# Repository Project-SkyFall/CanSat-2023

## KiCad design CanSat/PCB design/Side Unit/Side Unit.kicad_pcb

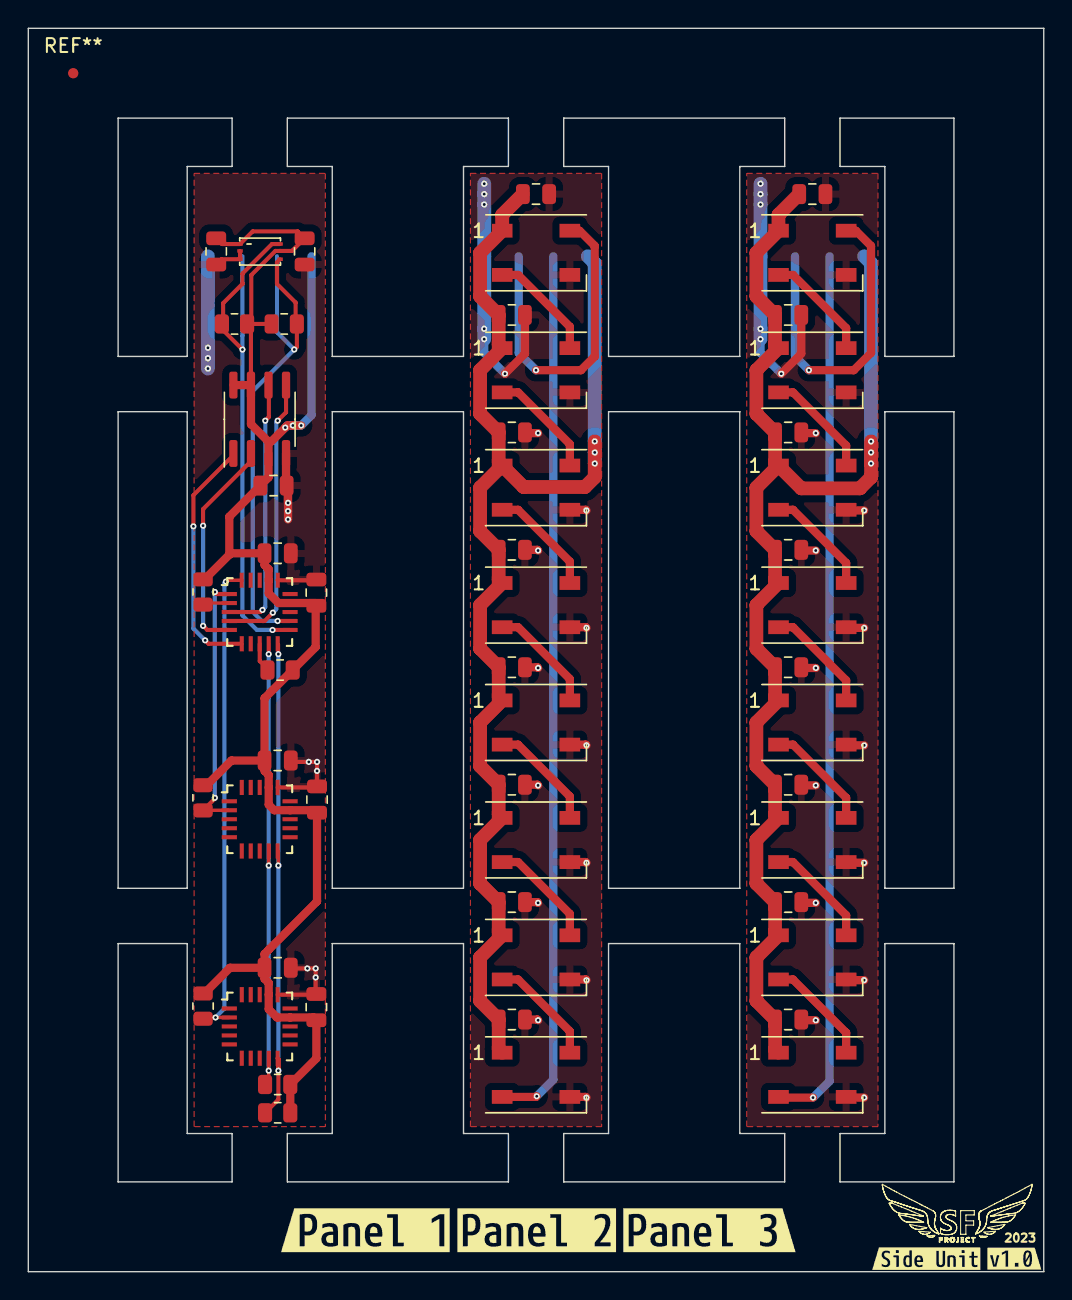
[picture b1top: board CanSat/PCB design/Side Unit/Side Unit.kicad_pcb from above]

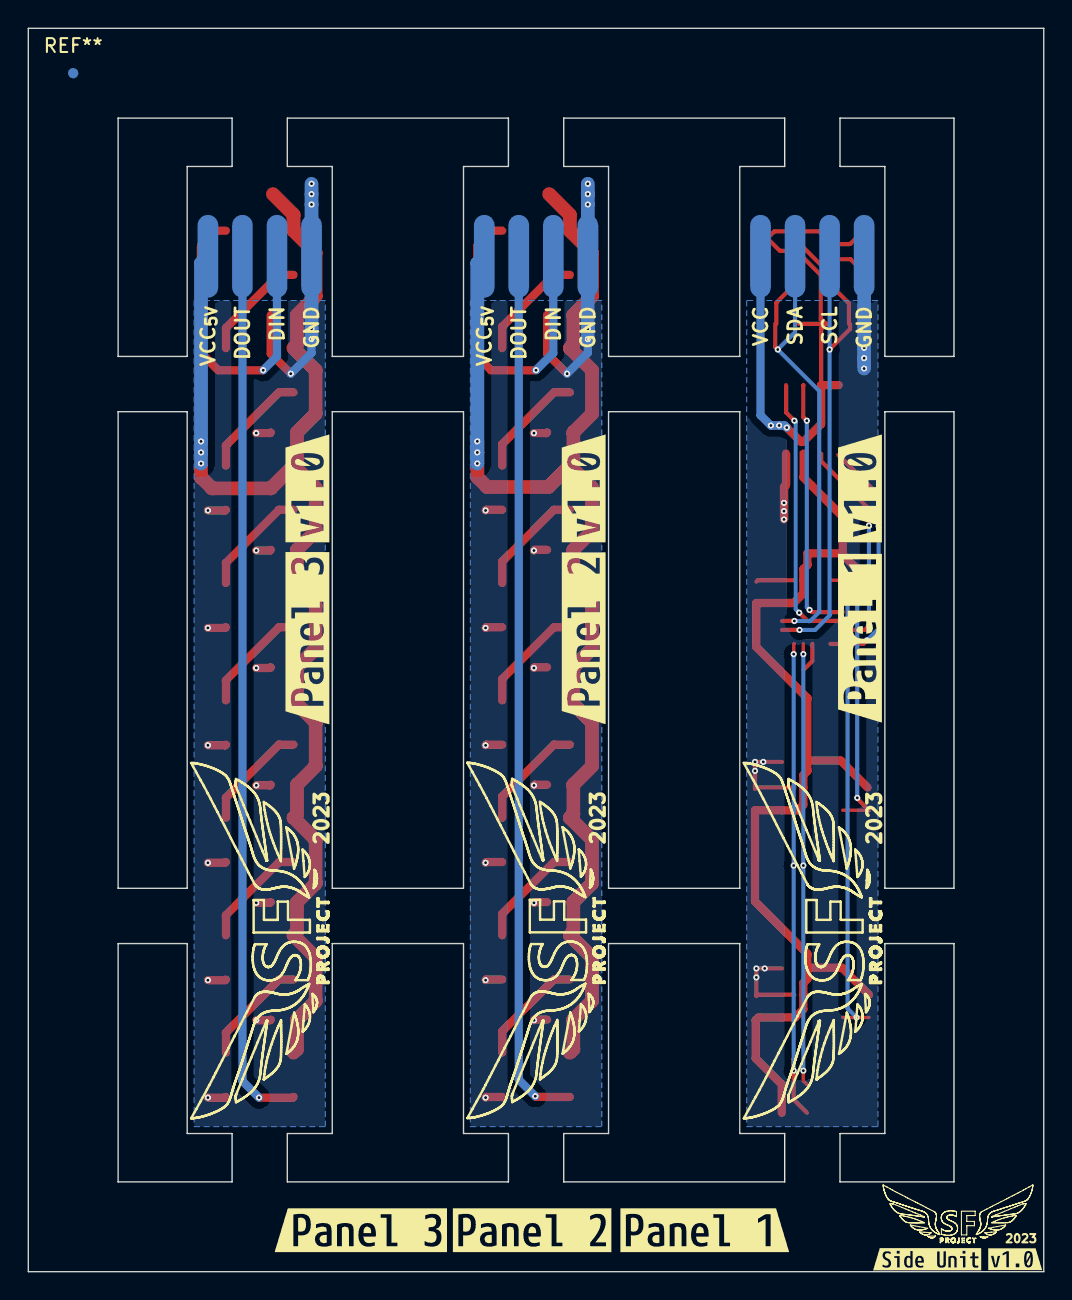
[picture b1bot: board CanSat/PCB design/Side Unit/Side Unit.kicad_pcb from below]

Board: 2 copper layers, 73.5 x 90.0 mm, 73 parts (14 on the bottom side), 36 nets.

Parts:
C301, C303, C305, C401, C402, C501, C502, C503, C504, C505, C506, C507, C508, C601, C602, C603, C604, C605, C606, C607, C608: 0.1uF; C_0805_2012Metric
C302, C304, C306, C307: 1uF; C_0805_2012Metric
D501, D502, D503, D504, D505, D506, D507, D508, D601, D602, D603, D604, D605, D606, D607, D608: WS2812B; LED_WS2812B_PLCC4_5.0x5.0mm_P3.2mm
J101, J102, J103: Land patern; Land-pattern
R201, R202, R301, R302, R303, R304, R305, R306: 10k; R_0805_2012Metric
U301: AS72651; AMS_LGA-20_4.7x4.5mm_P0.65mm
U302: AS72652; AMS_LGA-20_4.7x4.5mm_P0.65mm
U303: AS72653; AMS_LGA-20_4.7x4.5mm_P0.65mm
U304: AT25SF041B-SSHD-B; SOIC-8_3.9x4.9mm_P1.27mm
U401: BH1730; WSOF6
kibuzzard-63C42A2A: G***; kibuzzard-63C42A2A
kibuzzard-63C42A5F, kibuzzard-63C42A5F#2, kibuzzard-63C42A5F#3: G***; kibuzzard-63C42A5F
kibuzzard-63C42B4A: G***; kibuzzard-63C42B4A
kibuzzard-63C42B39: G***; kibuzzard-63C42B39
kibuzzard-63C86FC3: G***; kibuzzard-63C86FC3
kibuzzard-63C86FCE: G***; kibuzzard-63C86FCE
kibuzzard-63C685CC, kibuzzard-63C685CC#2: G***; kibuzzard-63C685CC
kibuzzard-63C685D8, kibuzzard-63C685D8#2: G***; kibuzzard-63C685D8
kibuzzard-63C6862F: G***; kibuzzard-63C6862F
kibuzzard-63C68642, kibuzzard-63C68642#2: G***; kibuzzard-63C68642
kibuzzard-63C68658: G***; kibuzzard-63C68658

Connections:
/Panel 1/GND: C301.2, C302.2, C303.2, C304.2, C305.2, C306.2, C307.2, C401.1, C402.2, J101.1, U301.16 (GND), U302.16 (GND), U303.16 (GND), U304.4 (GND), U401.2 (INT), U401.3 (GND)
/Panel 1/SCL: J101.2, R202.2, U301.11 (RX/SCL_S), U401.6 (SCL)
/Panel 1/SDA: J101.3, R201.2, U301.12 (TX/SDA_S), U401.4 (SDA)
/Panel 1/Spectroscope Unit/MISO: U301.5 (MISO), U304.2 (SO_(IO1_))
/Panel 1/Spectroscope Unit/MOSI: U301.4 (MOSI), U304.5 (SI_(IO0_))
/Panel 1/Spectroscope Unit/SCK: U301.3 (SCK), U304.6 (SCK)
/Panel 1/Spectroscope Unit/SCL_S: R304.2, U301.9 (SCL_M), U302.9 (SCL_S), U303.9 (SCL_S)
/Panel 1/Spectroscope Unit/SDA_S: R303.2, U301.10 (SDA_M), U302.10 (SDA_S), U303.10 (SDA_S)
/Panel 1/Spectroscope Unit/~CS: U301.6 (~CS), U304.1 (~CS)
/Panel 1/Spectroscope Unit/~RES: R306.2, U301.2 (~RES)
/Panel 1/Spectroscope Unit/~SLV1_RES: R302.2, U301.1 (~SLV1_RES), U302.2 (~RES)
/Panel 1/Spectroscope Unit/~SLV2_RES: R301.2, U301.20 (~SLV2_RES), U303.2 (~RES)
/Panel 1/VCC: C301.1, C302.1, C303.1, C304.1, C305.1, C306.1, C307.1, C401.2, C402.1, J101.4, R201.1, R202.1, R301.1, R302.1, R303.1, R304.1, R305.1, R306.1, U301.14 (VDD2), U301.17 (VDD1), U302.14 (VDD2), U302.17 (VDD1), U303.14 (VDD2), U303.17 (VDD1), U304.3 (~WP_(IO2_)), U304.7 (~HOLD_(IO3_)), U304.8 (VCC), U401.1 (VCC), U401.5 (DVI)
/Panel 2/DIN: D501.4 (DIN), J102.2
/Panel 2/DOUT: D508.2 (DOUT), J102.3
/Panel 2/GND: C501.1, C502.1, C503.1, C504.1, C505.1, C506.1, C507.1, C508.1, D501.3 (VSS), D502.3 (VSS), D503.3 (VSS), D504.3 (VSS), D505.3 (VSS), D506.3 (VSS), D507.3 (VSS), D508.3 (VSS), J102.1
/Panel 2/VCC_5V: C501.2, C502.2, C503.2, C504.2, C505.2, C506.2, C507.2, C508.2, D501.1 (VDD), D502.1 (VDD), D503.1 (VDD), D504.1 (VDD), D505.1 (VDD), D506.1 (VDD), D507.1 (VDD), D508.1 (VDD), J102.4
/Panel 3/DIN: D601.4 (DIN), J103.2
/Panel 3/DOUT: D608.2 (DOUT), J103.3
/Panel 3/GND: C601.1, C602.1, C603.1, C604.1, C605.1, C606.1, C607.1, C608.1, D601.3 (VSS), D602.3 (VSS), D603.3 (VSS), D604.3 (VSS), D605.3 (VSS), D606.3 (VSS), D607.3 (VSS), D608.3 (VSS), J103.1
/Panel 3/VCC_5V: C601.2, C602.2, C603.2, C604.2, C605.2, C606.2, C607.2, C608.2, D601.1 (VDD), D602.1 (VDD), D603.1 (VDD), D604.1 (VDD), D605.1 (VDD), D606.1 (VDD), D607.1 (VDD), D608.1 (VDD), J103.4
unnamed: D501.2 (DOUT), D502.4 (DIN)
unnamed: D502.2 (DOUT), D503.4 (DIN)
unnamed: D503.2 (DOUT), D504.4 (DIN)
unnamed: D504.2 (DOUT), D505.4 (DIN)
unnamed: D505.2 (DOUT), D506.4 (DIN)
unnamed: D506.2 (DOUT), D507.4 (DIN)
unnamed: D507.2 (DOUT), D508.4 (DIN)
unnamed: D601.2 (DOUT), D602.4 (DIN)
unnamed: D602.2 (DOUT), D603.4 (DIN)
unnamed: D603.2 (DOUT), D604.4 (DIN)
unnamed: D604.2 (DOUT), D605.4 (DIN)
unnamed: D605.2 (DOUT), D606.4 (DIN)
unnamed: D606.2 (DOUT), D607.4 (DIN)
unnamed: D607.2 (DOUT), D608.4 (DIN)
unnamed: R305.2, U301.8 (I2C_ENB)

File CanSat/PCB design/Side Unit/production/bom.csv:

Designator,Footprint,Quantity,Value,LCSC Part #
"C301, C303, C305, C401, C402, C501, C502, C503, C504, C505, C506, C507, C508, C601, C602, C603, C604, C605, C606, C607, C608",C_0805_2012Metric,21,100nF,
"C302, C304, C306, C307",C_0805_2012Metric,4,1uF,
"D501, D502, D503, D504, D505, D506, D507, D508, D601, D602, D603, D604, D605, D606, D607, D608",LED_WS2812B_PLCC4_5.0x5.0mm_P3.2mm,16,WS2812B,
"R201, R202, R301, R302, R303, R304, R305, R306",R_0805_2012Metric,8,10k,
U301,AMS_LGA-20_4.7x4.5mm_P0.65mm,1,AS72651,
U302,AMS_LGA-20_4.7x4.5mm_P0.65mm,1,AS72652,
U303,AMS_LGA-20_4.7x4.5mm_P0.65mm,1,AS72653,
U304,SOIC-8_3.9x4.9mm_P1.27mm,1,AT25SF041B-SSHD-B,
U401,WSOF6,1,BH1730,

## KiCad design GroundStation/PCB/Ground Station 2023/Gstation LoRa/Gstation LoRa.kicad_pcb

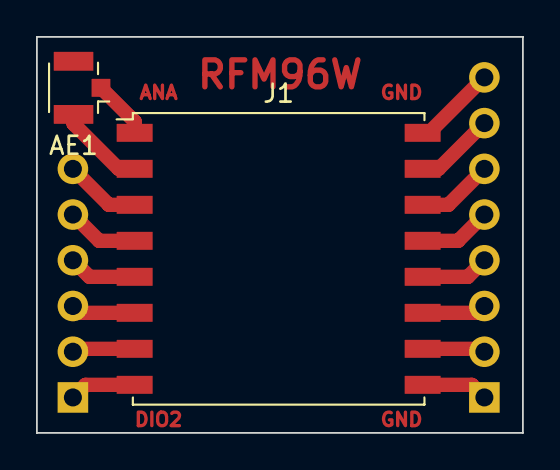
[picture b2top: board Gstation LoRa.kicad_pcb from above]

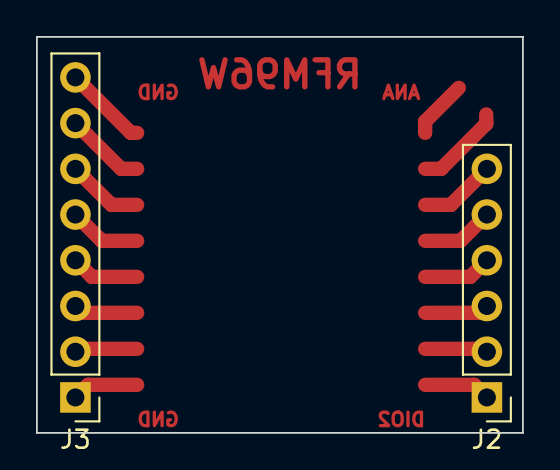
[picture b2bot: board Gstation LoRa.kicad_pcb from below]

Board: 2 copper layers, 27.0 x 22.0 mm, 4 parts (2 on the bottom side), 16 nets.

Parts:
AE1: Antenna_Shield; U.FL_Hirose_U.FL-R-SMT-1_Vertical
J1: Conn_02x08_Counter_Clockwise; HOPERF_RFM9XW_SMD
J2: Conn_01x06_Male; PinHeader_1x06_P2.54mm_Vertical
J3: Conn_01x08_Male; PinHeader_1x08_P2.54mm_Vertical

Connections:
unnamed: AE1.1 (A), J1.1
unnamed: AE1.2 (Shield), J1.2
unnamed: J1.3, J2.6
unnamed: J1.4, J2.5
unnamed: J1.5, J2.4
unnamed: J1.6, J2.3
unnamed: J1.7, J2.2
unnamed: J1.8, J2.1
unnamed: J1.9, J3.1
unnamed: J1.10, J3.2
unnamed: J1.11, J3.3
unnamed: J1.12, J3.4
unnamed: J1.13, J3.5
unnamed: J1.14, J3.6
unnamed: J1.15, J3.7
unnamed: J1.16, J3.8

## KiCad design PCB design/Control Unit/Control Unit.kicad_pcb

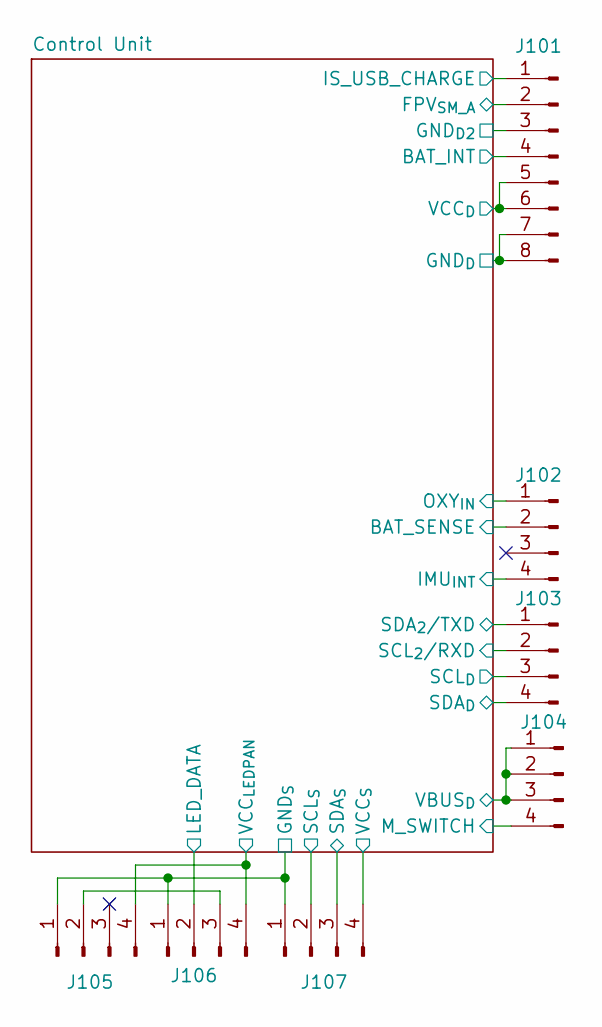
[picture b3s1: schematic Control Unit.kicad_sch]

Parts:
J101: Conn_02x04_Male; PinHeader_2x04_P2.54mm_Vertical
J102, J103, J104: Conn_02x02_Male; PinHeader_2x02_P2.54mm_Vertical
J105, J106, J107: 009155004541006

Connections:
/Control Unit/BATT_INT: J101.4; also elsewhere on the board
/Control Unit/BAT_SENSE: J102.2; also elsewhere on the board
/Control Unit/FPV_{SM_A}: J101.2; also elsewhere on the board
/Control Unit/GND: J101.3, J101.7, J101.8, J105.1, J106.1, J107.1; also elsewhere on the board
/Control Unit/IMU_{INT}: J102.4; also elsewhere on the board
/Control Unit/IS_USB_CHARGE: J101.1; also elsewhere on the board
/Control Unit/LED_DATA: J106.2; also elsewhere on the board
/Control Unit/M_SWITCH: J104.4; also elsewhere on the board
/Control Unit/OXY_{IN}: J102.1; also elsewhere on the board
/Control Unit/SCL: J103.3, J107.2; also elsewhere on the board
/Control Unit/SCL_{2}/RXD: J103.2; also elsewhere on the board
/Control Unit/SDA: J103.4, J107.3; also elsewhere on the board
/Control Unit/SDA_{2}/TXD: J103.1; also elsewhere on the board
/Control Unit/VBUS: J104.1, J104.2, J104.3; also elsewhere on the board
/Control Unit/VCC: J101.5, J101.6, J107.4; also elsewhere on the board
/Control Unit/VCC_{LEDPAN}: J105.4, J106.4; also elsewhere on the board
unnamed: J105.2, J106.3

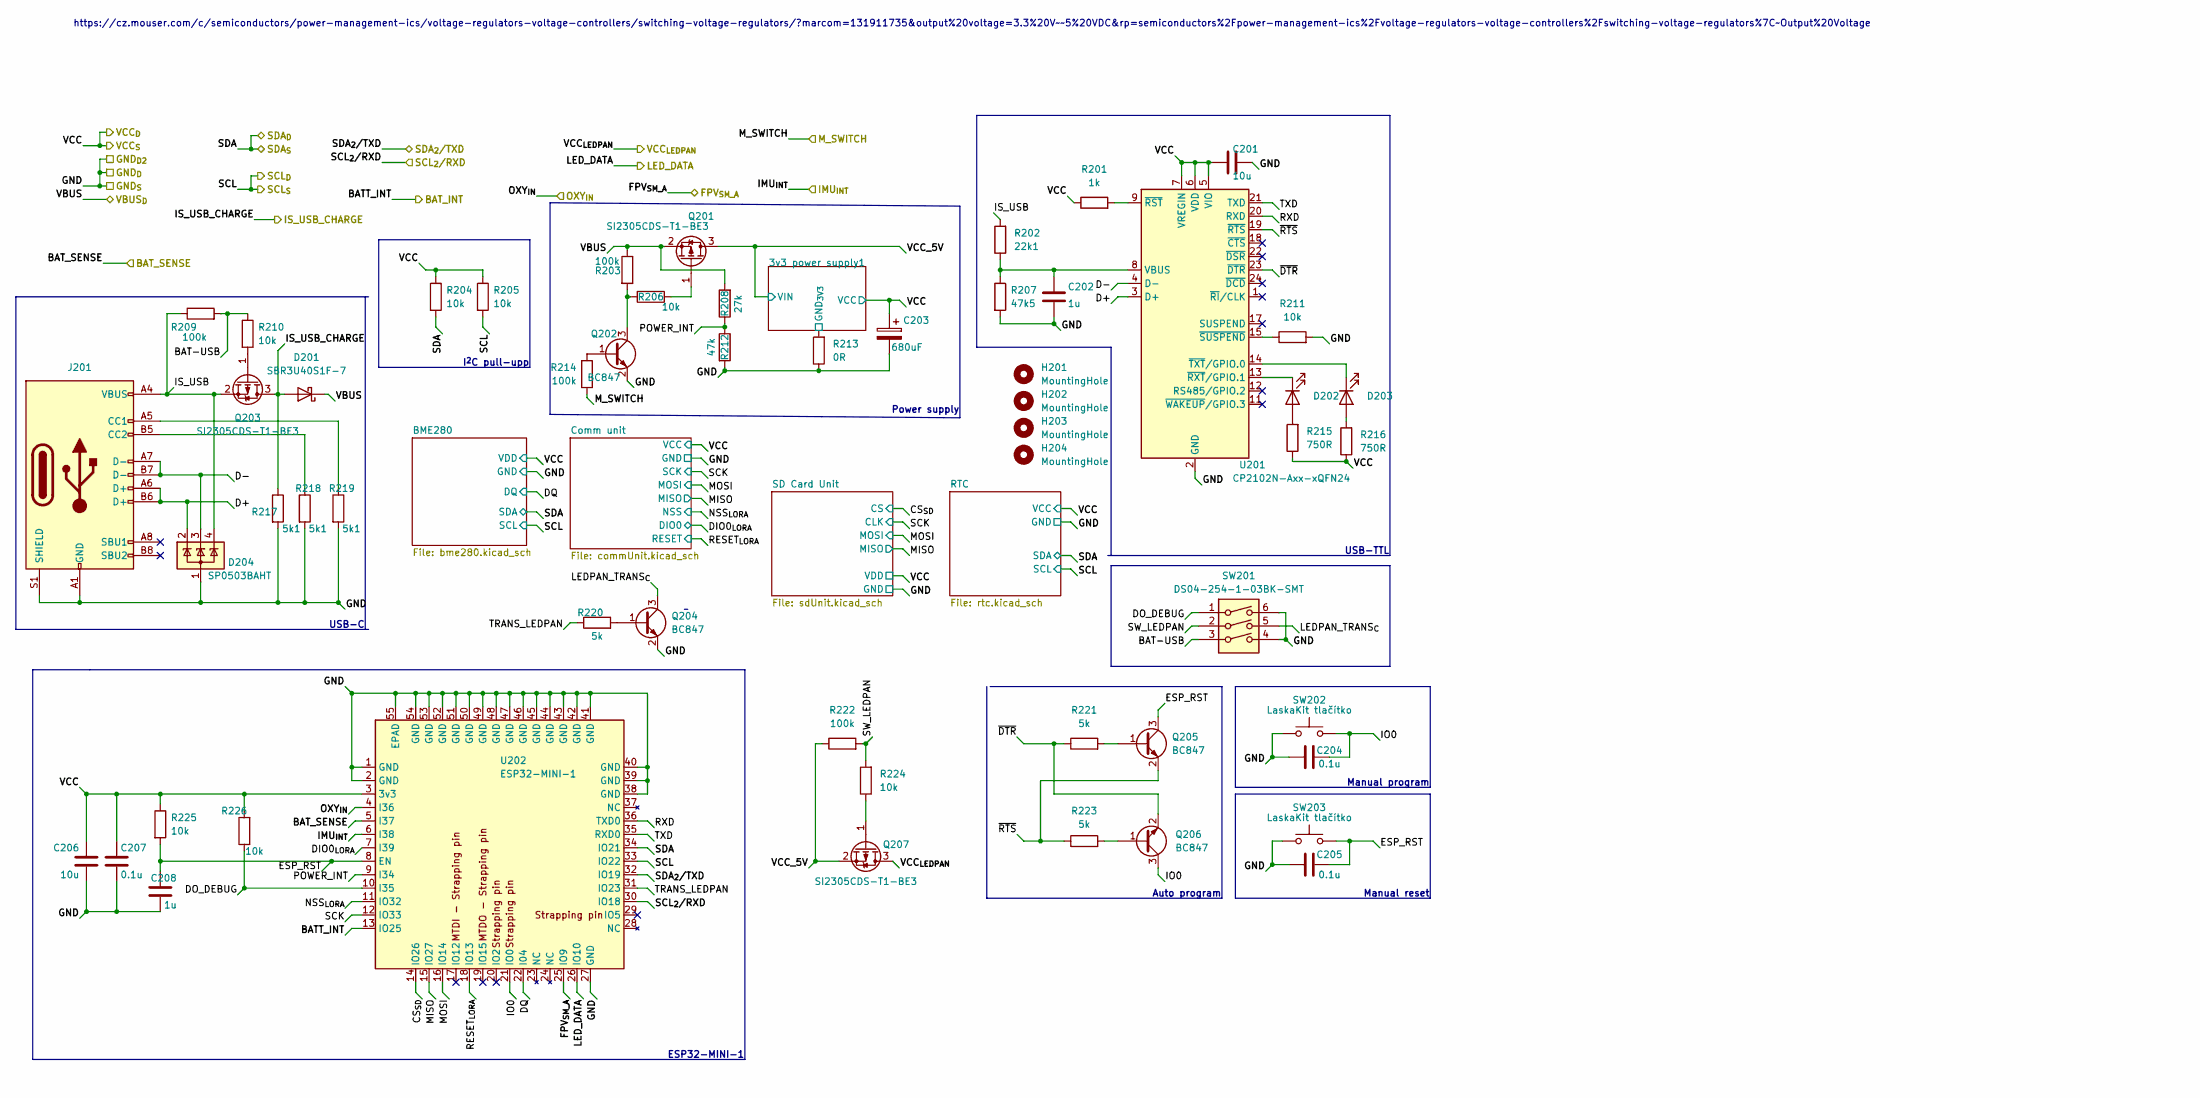
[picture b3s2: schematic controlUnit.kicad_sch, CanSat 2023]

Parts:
C201, C206: 10u; C_0805_2012Metric
C202, C208: 1u; C_0805_2012Metric
C203: 680uF; CP_Elec_6.3x7.7
C204, C205, C207: 0.1u; C_0805_2012Metric
D201: SBR3U40S1F-7; D_SOD-123F
D202, D203: APT2012LSECK/J4-PRV; LED_0805_2012Metric
D204: SP0503BAHT; SOT-143
H201, H202, H203, H204: MountingHole; MountingHole_3.2mm_M3
J201: USB4110-GF-A; USB4110GFA
Q201, Q203, Q207: SI2305CDS-T1-BE3; SOT-23
Q202, Q204, Q205, Q206: BC847; SOT-23
R201: 1k; R_0805_2012Metric
R202: 22k1; R_0805_2012Metric
R203, R209, R214, R222: 100k; R_0805_2012Metric
R204, R205, R206, R210, R211, R224, R225, R226: 10k; R_0805_2012Metric
R207: 47k5; R_0805_2012Metric
R208: 27k; R_0805_2012Metric
R212: 47k; R_0805_2012Metric
R213: 0R; R_1206_3216Metric
R215, R216: 750R; R_0805_2012Metric
R217, R218, R219: 5k1; R_0805_2012Metric
R220, R221, R223: 5k; R_0805_2012Metric
SW201: DS04-254-1-03BK-SMT; SW_DIP_SPSTx03_Slide_Omron_A6S-310x_W8.9mm_P2.54mm
SW202, SW203: LaskaKit tlačítko; Tlačítko SMD LaskaKit
U201: CP2102N-Axx-xQFN24; QFN-24-1EP_4x4mm_P0.5mm_EP2.6x2.6mm
U202: ESP32-MINI-1

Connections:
/Control Unit/3v3 power supply1/GND_{3V3}: R213.2; also elsewhere on the board
/Control Unit/BAT-USB: R209.2, R210.1, SW201.3
/Control Unit/BATT_INT: U202.13 (IO25); also elsewhere on the board
/Control Unit/BAT_SENSE: U202.5 (I37); also elsewhere on the board
/Control Unit/CS_{SD}: U202.14 (IO26); also elsewhere on the board
/Control Unit/D+: D204.2 (K), J201.A6 (D+), J201.B6 (D+), U201.3 (D+)
/Control Unit/D-: D204.3 (K), J201.A7 (D-), J201.B7 (D-), U201.4 (D-)
/Control Unit/DIO0_{LORA}: U202.7 (I39); also elsewhere on the board
/Control Unit/DO_DEBUG: R226.1, SW201.1, U202.10 (I35)
/Control Unit/DQ: U202.22 (I04); also elsewhere on the board
/Control Unit/ESP_RST: C205.2, C208.1, Q205.3 (C), R225.2, SW203.2, U202.8 (EN)
/Control Unit/FPV_{SM_A}: U202.25 (IO9); also elsewhere on the board
/Control Unit/GND: C201.2, C202.2, C203.2, C204.1, C205.1, C206.2, C207.2, C208.2, D204.1 (A), J201.A1 (GND), J201.A12 (GND), J201.B1 (GND), J201.B12 (GND), J201.S1 (SHIELD), Q202.2 (E), Q204.2 (E), R207.2, R211.2, R212.2, R213.1, R217.2, R218.2, R219.2, SW201.4, SW201.6, SW202.1, SW203.1, U201.2 (GND), U201.25 (GND), U202.1 (GND), U202.2 (GND), U202.27 (GND), U202.38 (GND), U202.39 (GND), U202.40 (GND), U202.41 (GND), U202.42 (GND), U202.43 (GND), U202.44 (GND), U202.45 (GND), U202.46 (GND), U202.47 (GND), U202.48 (GND), U202.49 (GND), U202.50 (GND), U202.51 (GND), U202.52 (GND), U202.53 (GND), U202.54 (GND), U202.55 (EPAD); also elsewhere on the board
/Control Unit/IMU_{INT}: U202.6 (I38); also elsewhere on the board
/Control Unit/IO0: C204.2, Q206.3 (C), SW202.2, U202.21 (IO0)
/Control Unit/IS_USB: D204.4 (K), J201.A4 (VBUS), J201.A9 (VBUS), J201.B4 (VBUS), J201.B9 (VBUS), Q203.2 (S), R202.2, R209.1
/Control Unit/IS_USB_CHARGE: D201.2 (A), Q203.3 (D), R217.1; also elsewhere on the board
/Control Unit/LEDPAN_TRANS_{C}: Q204.3 (C), SW201.5
/Control Unit/LED_DATA: U202.26 (IO10); also elsewhere on the board
/Control Unit/MISO: U202.15 (IO27); also elsewhere on the board
/Control Unit/MOSI: U202.16 (IO14); also elsewhere on the board
/Control Unit/M_SWITCH: R214.1; also elsewhere on the board
/Control Unit/NSS_{LORA}: U202.11 (IO32); also elsewhere on the board
/Control Unit/OXY_{IN}: U202.4 (I36); also elsewhere on the board
/Control Unit/POWER_INT: R208.1, R212.1, U202.9 (I34)
/Control Unit/RESET_{LORA}: U202.18 (IO13); also elsewhere on the board
/Control Unit/RXD: U201.20 (RXD), U202.36 (TXD0)
/Control Unit/SCK: U202.12 (IO33); also elsewhere on the board
/Control Unit/SCL: R205.2, U202.33 (IO22); also elsewhere on the board
/Control Unit/SCL_{2}/RXD: U202.30 (IO18); also elsewhere on the board
/Control Unit/SDA: R204.2, U202.34 (IO21); also elsewhere on the board
/Control Unit/SDA_{2}/TXD: U202.32 (IO19); also elsewhere on the board
/Control Unit/SW_LEDPAN: R222.2, R224.2, SW201.2
/Control Unit/TRANS_LEDPAN: R220.1, U202.31 (IO23)
/Control Unit/TXD: U201.21 (TXD), U202.35 (RXD0)
/Control Unit/VBUS: D201.1 (K), Q201.2 (S), R203.1, R208.2; also elsewhere on the board
/Control Unit/VCC: C201.1, C203.1, C206.1, C207.1, R201.1, R204.1, R205.1, R215.1, R216.1, R225.1, R226.2, U201.5 (VIO), U201.6 (VDD), U201.7 (VREGIN), U202.3 (3v3); also elsewhere on the board
/Control Unit/VCC_5V: Q201.3 (D), Q207.2 (S), R222.1; also elsewhere on the board
/Control Unit/VCC_{LEDPAN}: Q207.3 (D); also elsewhere on the board
/Control Unit/~DTR: Q206.2 (E), R221.1, U201.23 (~DTR)
/Control Unit/~RTS: Q205.2 (E), R223.1, U201.19 (~RTS)
unnamed: C202.1, R202.1, R207.1, U201.8 (VBUS)
unnamed: D202.1 (K), U201.13 (~RXT/GPIO.1)
unnamed: D202.2 (A), R215.2
unnamed: D203.1 (K), U201.14 (~TXT/GPIO.0)
unnamed: D203.2 (A), R216.2
unnamed: J201.A5 (CC1), R219.1
unnamed: J201.B5 (CC2), R218.1
unnamed: Q201.1 (G), R206.1
unnamed: Q202.1 (B), R214.2
unnamed: Q202.3 (C), R203.2, R206.2
unnamed: Q203.1 (G), R210.2
unnamed: Q204.1 (B), R220.2
unnamed: Q205.1 (B), R221.2
unnamed: Q206.1 (B), R223.2
unnamed: Q207.1 (G), R224.1
unnamed: R201.2, U201.9 (~RST)
unnamed: R211.1, U201.15 (~SUSPEND)

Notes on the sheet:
USB-TTL
I^{2}C pull-upp
Auto program
ESP32-MINI-1
USB-C
Power supply
Manual reset
https://cz.mouser.com/c/semiconductors/power-management-ics/voltage-regulators-voltage-controllers/switching-voltage-regulators/?marcom=131911735&output%20voltage=3.3%20V~~5%20VDC&rp=semiconductors%2Fpower-management-ics%2Fvoltage-regulators-voltage-controllers%2Fswitching-voltage-regulators%7C~Out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
Manual program

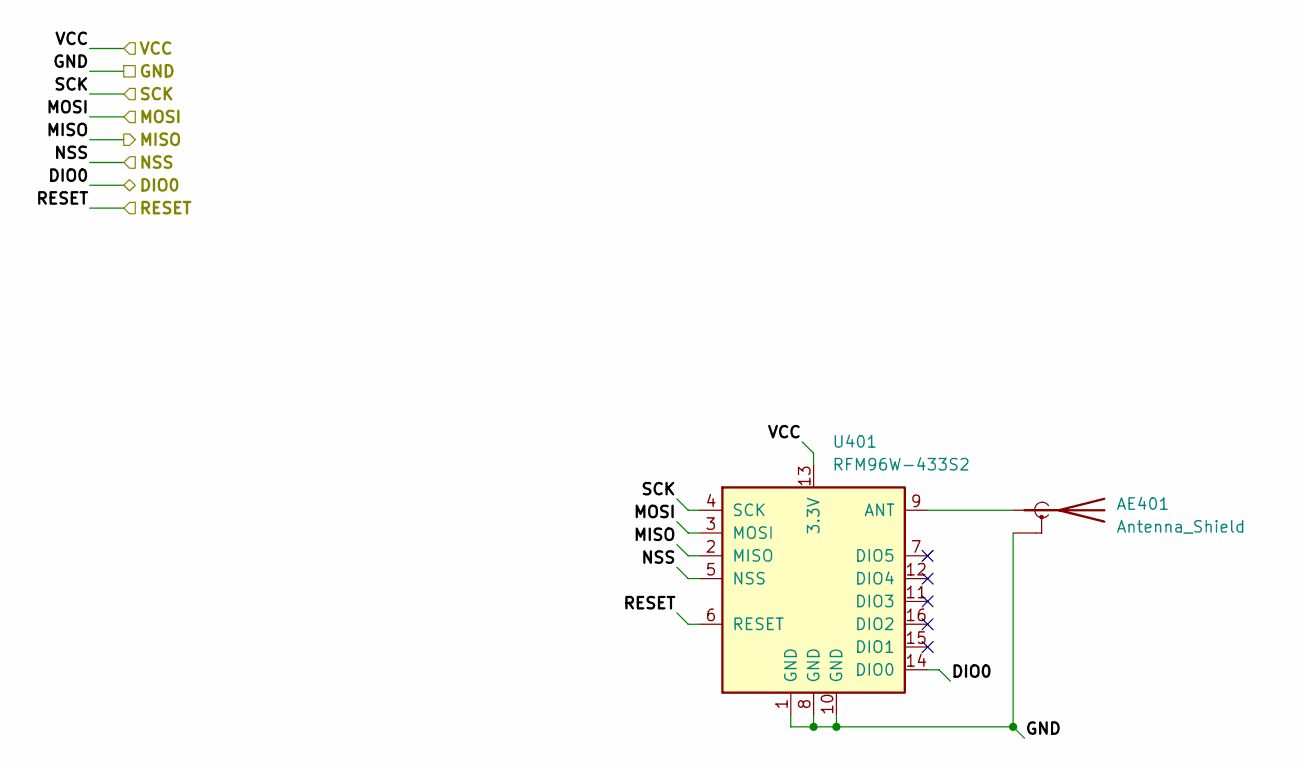
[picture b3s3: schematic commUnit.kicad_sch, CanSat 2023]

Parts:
AE401: Antenna_Shield; U.FL_Hirose_U.FL-R-SMT-1_Vertical
U401: RFM96W-433S2; HOPERF_RFM9XW_SMD

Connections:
/Control Unit/DIO0_{LORA}: U401.14 (DIO0); also elsewhere on the board
/Control Unit/GND: AE401.2 (Shield), U401.1 (GND), U401.8 (GND), U401.10 (GND); also elsewhere on the board
/Control Unit/MISO: U401.2 (MISO); also elsewhere on the board
/Control Unit/MOSI: U401.3 (MOSI); also elsewhere on the board
/Control Unit/NSS_{LORA}: U401.5 (NSS); also elsewhere on the board
/Control Unit/RESET_{LORA}: U401.6 (RESET); also elsewhere on the board
/Control Unit/SCK: U401.4 (SCK); also elsewhere on the board
/Control Unit/VCC: U401.13 (3.3V); also elsewhere on the board
unnamed: AE401.1 (A), U401.9 (ANT)

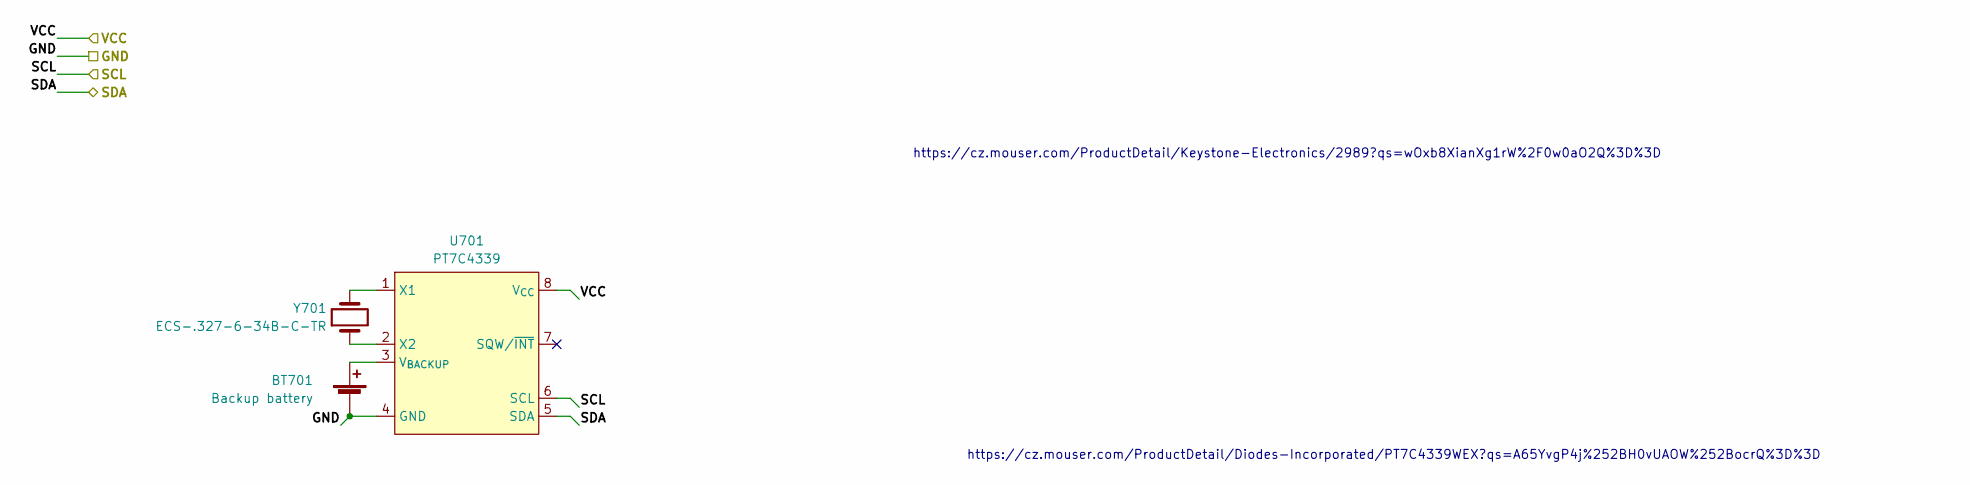
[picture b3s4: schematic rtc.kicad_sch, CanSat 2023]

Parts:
BT701: Backup battery; 2989
U701: PT7C4339; SOIC-8-1EP_3.9x4.9mm_P1.27mm_EP2.29x3mm
Y701: ECS-.327-6-34B-C-TR; ECX-31B

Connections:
/Control Unit/GND: BT701.2 (-), U701.4 (GND); also elsewhere on the board
/Control Unit/SCL: U701.6 (SCL); also elsewhere on the board
/Control Unit/SDA: U701.5 (SDA); also elsewhere on the board
/Control Unit/VCC: U701.8 (V_{CC}); also elsewhere on the board
unnamed: BT701.1 (+), U701.3 (V_{BACKUP})
unnamed: U701.1 (X1), Y701.2
unnamed: U701.2 (X2), Y701.1

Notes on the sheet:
https://cz.mouser.com/ProductDetail/Keystone-Electronics/2989?qs=wOxb8XianXg1rW%2F0w0aO2Q%3D%3D
https://cz.mouser.com/ProductDetail/Diodes-Incorporated/PT7C4339WEX?qs=A65YvgP4j%252BH0vUAOW%252BocrQ%3D%3D

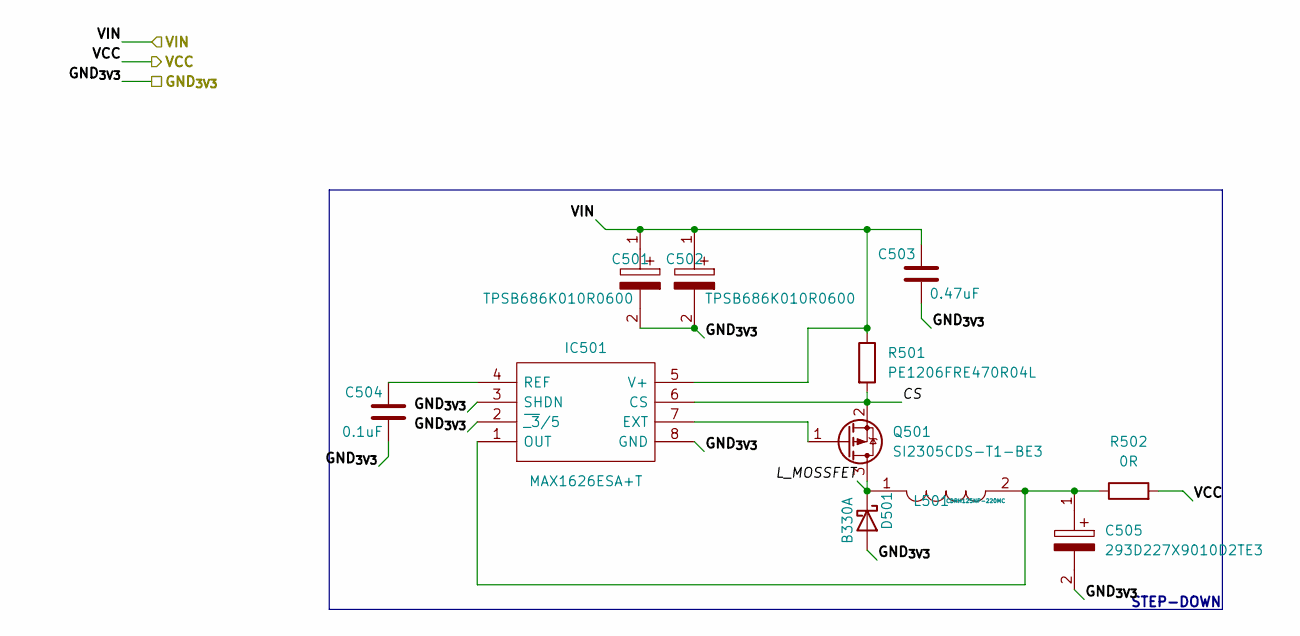
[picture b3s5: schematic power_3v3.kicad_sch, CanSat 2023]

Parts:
C501, C502: TPSB686K010R0600; CP_EIA-3528-21_Kemet-B; Mouser Part Number 581-TPSB686K010R0600
C503: 0.47uF; C_0805_2012Metric
C504: 0.1uF; C_0805_2012Metric
C505: 293D227X9010D2TE3; CP_EIA-7343-31_Kemet-D; Mouser Part Number 74-293D227X9010D2TE3
D501: B330A; D_SMA
IC501: MAX1626ESA+T; SOIC127P600X175-8N; Mouser Part Number 700-MAX1626ESAT
L501: CDRH125NP-220MC; CDRH125101MC; Mouser Part Number 851-CDRH125NP-220MC
Q501: SI2305CDS-T1-BE3; SOT-23
R501: PE1206FRE470R04L; R_1206_Current
R502: 0R; R_1206_3216Metric

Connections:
/Control Unit/3v3 power supply1/CS: IC501.6 (CS), Q501.2 (S), R501.2
/Control Unit/3v3 power supply1/GND_{3V3}: C501.2, C502.2, C503.2, C504.2, C505.2, D501.2 (A), IC501.2 (~_3/5), IC501.3 (SHDN), IC501.8 (GND); also elsewhere on the board
/Control Unit/3v3 power supply1/L_MOSSFET: D501.1 (K), L501.1, Q501.3 (D)
/Control Unit/VCC: R502.2; also elsewhere on the board
/Control Unit/VCC_5V: C501.1, C502.1, C503.1, IC501.5 (V+), R501.1; also elsewhere on the board
unnamed: C504.1, IC501.4 (REF)
unnamed: C505.1, IC501.1 (OUT), L501.2, R502.1
unnamed: IC501.7 (EXT), Q501.1 (G)

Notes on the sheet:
STEP-DOWN

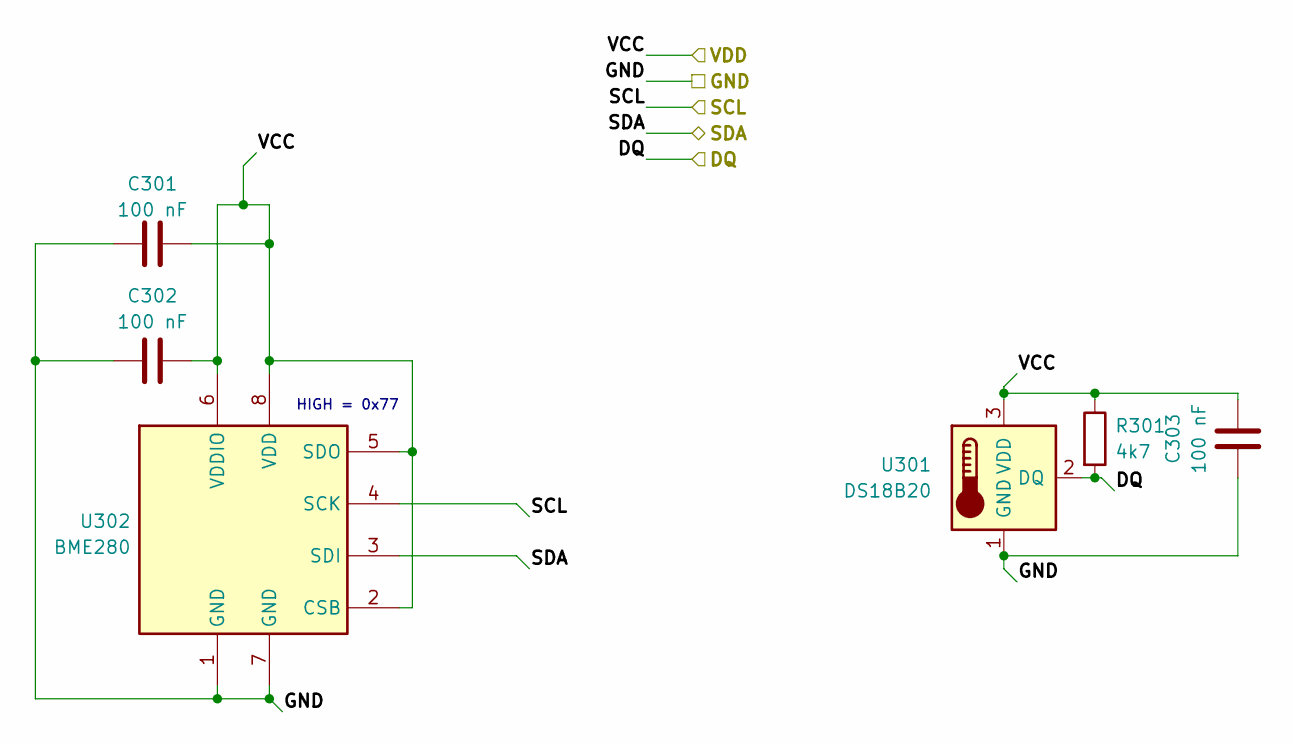
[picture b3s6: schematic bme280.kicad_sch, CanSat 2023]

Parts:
C301, C302, C303: 100 nF; C_0805_2012Metric
R301: 4k7; R_0805_2012Metric
U301: DS18B20; TO-92_Inline
U302: BME280; Bosch_LGA-8_2.5x2.5mm_P0.65mm_ClockwisePinNumbering

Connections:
/Control Unit/DQ: R301.2, U301.2 (DQ); also elsewhere on the board
/Control Unit/GND: C301.2, C302.2, C303.2, U301.1 (GND), U302.1 (GND), U302.7 (GND); also elsewhere on the board
/Control Unit/SCL: U302.4 (SCK); also elsewhere on the board
/Control Unit/SDA: U302.3 (SDI); also elsewhere on the board
/Control Unit/VCC: C301.1, C302.1, C303.1, R301.1, U301.3 (VDD), U302.2 (CSB), U302.5 (SDO), U302.6 (VDDIO), U302.8 (VDD); also elsewhere on the board

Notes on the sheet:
HIGH = 0x77

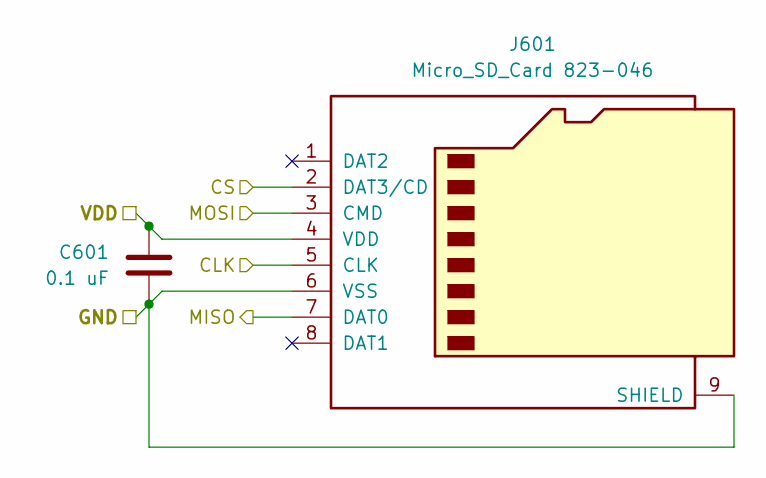
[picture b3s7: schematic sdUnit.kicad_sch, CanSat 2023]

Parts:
C601: 0.1 uF; C_0805_2012Metric
J601: Micro_SD_Card 823-046; DS1139-05

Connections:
/Control Unit/CS_{SD}: J601.2 (DAT3/CD); also elsewhere on the board
/Control Unit/GND: C601.1, J601.6 (VSS), J601.9 (SHIELD); also elsewhere on the board
/Control Unit/MISO: J601.7 (DAT0); also elsewhere on the board
/Control Unit/MOSI: J601.3 (CMD); also elsewhere on the board
/Control Unit/SCK: J601.5 (CLK); also elsewhere on the board
/Control Unit/VCC: C601.2, J601.4 (VDD); also elsewhere on the board
